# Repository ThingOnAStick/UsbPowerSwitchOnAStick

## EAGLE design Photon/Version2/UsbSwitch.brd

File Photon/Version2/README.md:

Usb Power Switch On A Stick
---------------------------

Control USB Power outlet to 2 USB A sockets via Photon.

Faults:
* V2.01
** ....
* V2.00
** 3v3 not connected to off board connector (D6/D6/GND/VBatt/RST/3v3).
** Excess top layer fill at Photon Keepout shown on PCB view (pdf issue only)

Changes:
* V2.00 - Added second USB A Socket. Removed current monitor, Added jumpers for TX/RX + 5V, A3-A5 + 5V, D6-D7 + 3v3 + RST and VBatt. New board size. Added gnd screen to USB A sockets.
* V2.01
** Fixed missing 3v3 trace for JP1. Improved silk screen. 
** Breaking: Moved control/flag D1-D4 -> D2-D5. Added JP4 to export D0/D1 for SDA/SCL or Switch 1+2 external. With 3v3 and 5V on connector.
** Moved JP1/2/3 to have 0.1" grid seperation between JP1 side and JP2/3. Moved JP4 to be on 0.1" grid with JP1/2/3 to allow for daughter board fitting on top with easy 0.1 grid.
** Beefed up vias for GND connection between USB Plug and PCB Bottom.
** Increased USB -> IC2 power trace to 0.05 (from 0.04)
** Moved Socket B -> R2 voltage monitor input via to be at top of board rather than crossing Photon Keepout area

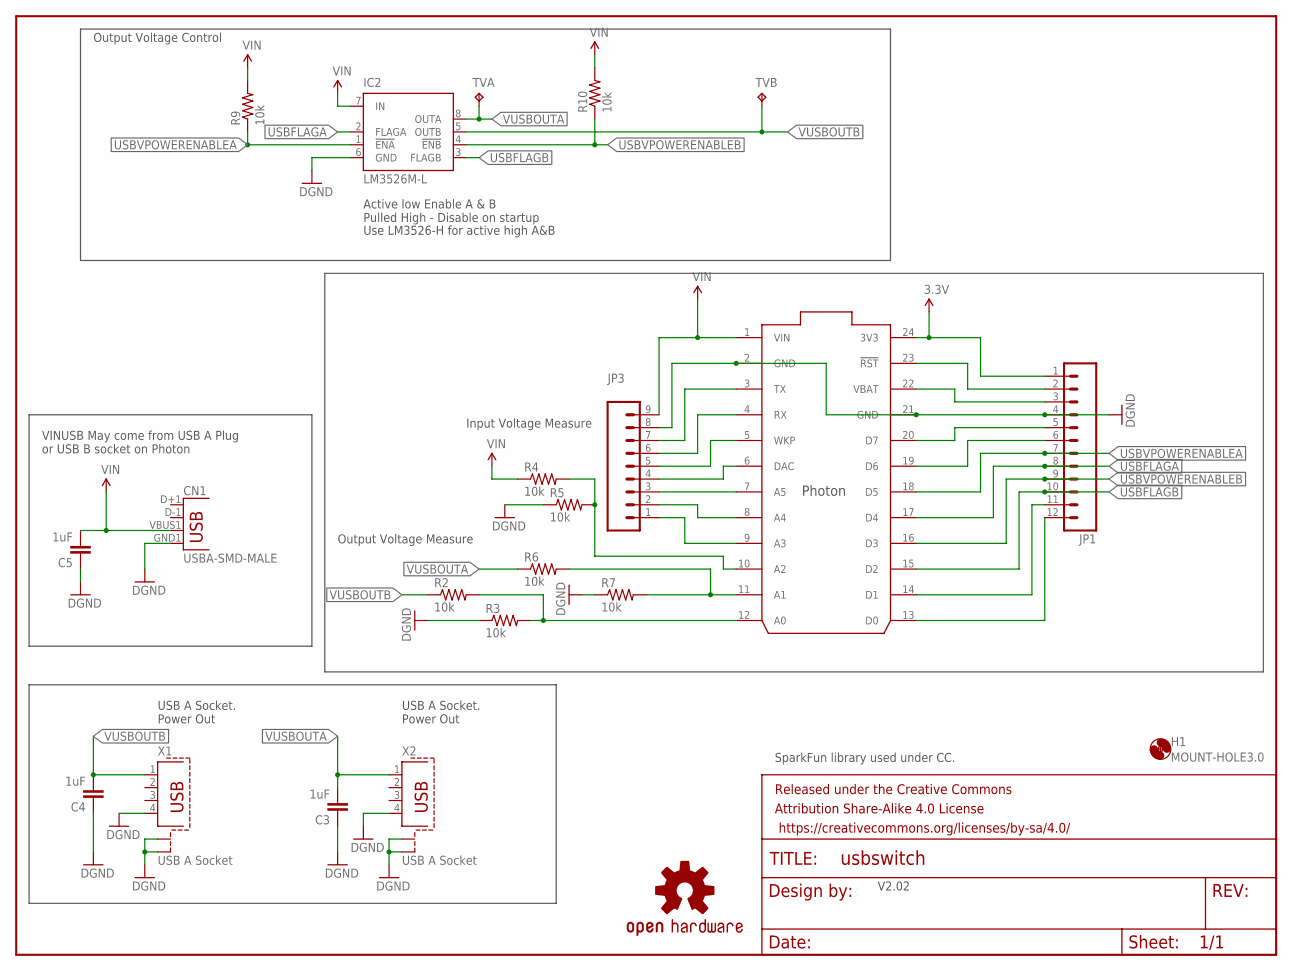
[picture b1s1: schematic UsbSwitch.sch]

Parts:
C3, C4, C5: 1uF; 0805
CN1: USBA-SMD-MALE; USB-A-SMT-MALE
FRAME2: FRAME-LETTER; CREATIVE_COMMONS
H1: MOUNT-HOLE3.0; 3,0
IC1: PHOTON
IC2: LM3526M-L; SO08
JP1: M12PTH; 1X12
JP3: M09; 1X09
LOGO2: OSHW-LOGOM; OSHW-LOGO-M
R2, R3, R4, R5, R6, R7, R9, R10: 10k; 1206
TVA: TPTP20SQ; TP20SQ
TVB: TPTP20SQ; TP20SQ
X1, X2: USB A Socket; PN87520-S

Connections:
3.3V: IC1.24 (3V3), JP1.1
GND: C3.1, C4.1, C5.1, CN1.GND1 (GND), IC1.2 (GND), IC1.21 (GND), IC2.6 (GND), JP1.4, JP3.8, R3.1, R5.1, R7.1, X1.4, X1.S1, X1.S2, X2.4, X2.S1, X2.S2
unnamed: IC1.6 (DAC), JP3.4
unnamed: IC1.5 (WKP), JP3.5
unnamed: IC1.4 (RX), JP3.6
unnamed: IC1.11 (A1), R6.2, R7.2
unnamed: IC1.9 (A3), JP3.1
unnamed: IC1.8 (A4), JP3.2
unnamed: IC1.7 (A5), JP3.3
unnamed: IC1.19 (D6), JP1.6
unnamed: IC1.20 (D7), JP1.5
unnamed: IC1.22 (VBAT), JP1.3
unnamed: IC1.23 (!RST), JP1.2
unnamed: IC1.3 (TX), JP3.7
unnamed: IC1.12 (A0), R2.2, R3.2
unnamed: IC1.10 (A2), R4.2, R5.2
SCL/SWITCH2: IC1.14 (D1), JP1.11
SDA/SWITCH1: IC1.13 (D0), JP1.12
USBFLAGA: IC1.17 (D4), IC2.2 (FLAGA), JP1.8
USBFLAGB: IC1.15 (D2), IC2.3 (FLAGB), JP1.10
USBVPOWERENABLEA: IC1.18 (D5), IC2.1 (!ENA), JP1.7, R9.1
USBVPOWERENABLEB: IC1.16 (D3), IC2.4 (!ENB), JP1.9, R10.1
VIN: C5.2, CN1.VBUS1 (VBUS), IC1.1 (VIN), IC2.7 (IN), JP3.9, R4.1, R9.2, R10.2
VUSBOUTA: C3.2, IC2.8 (OUTA), R6.1, TVA.TP, X2.1
VUSBOUTB: C4.2, IC2.5 (OUTB), R2.1, TVB.TP, X1.1

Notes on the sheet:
VINUSB May come from USB A Plug or USB B socket on Photon
USB A Socket. Power Out
Output Voltage Measure
Input Voltage Measure
Output Voltage Control
V2.02
Active low Enable A & B Pulled High - Disable on startup
Use LM3526-H for active high A&B
SparkFun library used under CC.

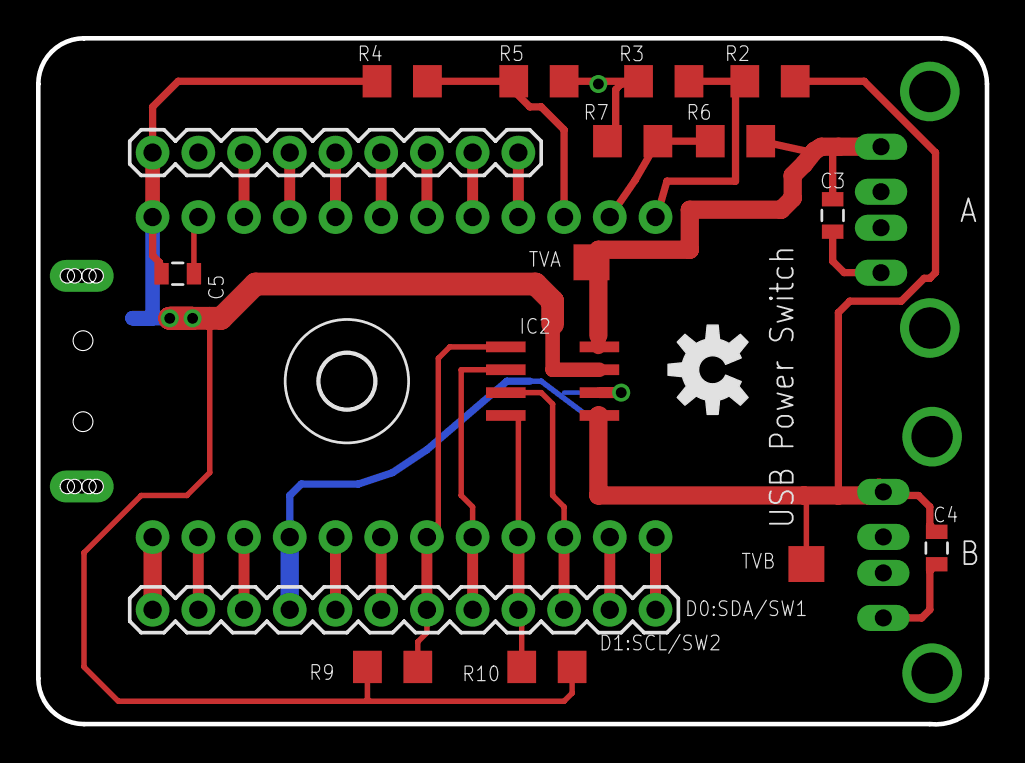
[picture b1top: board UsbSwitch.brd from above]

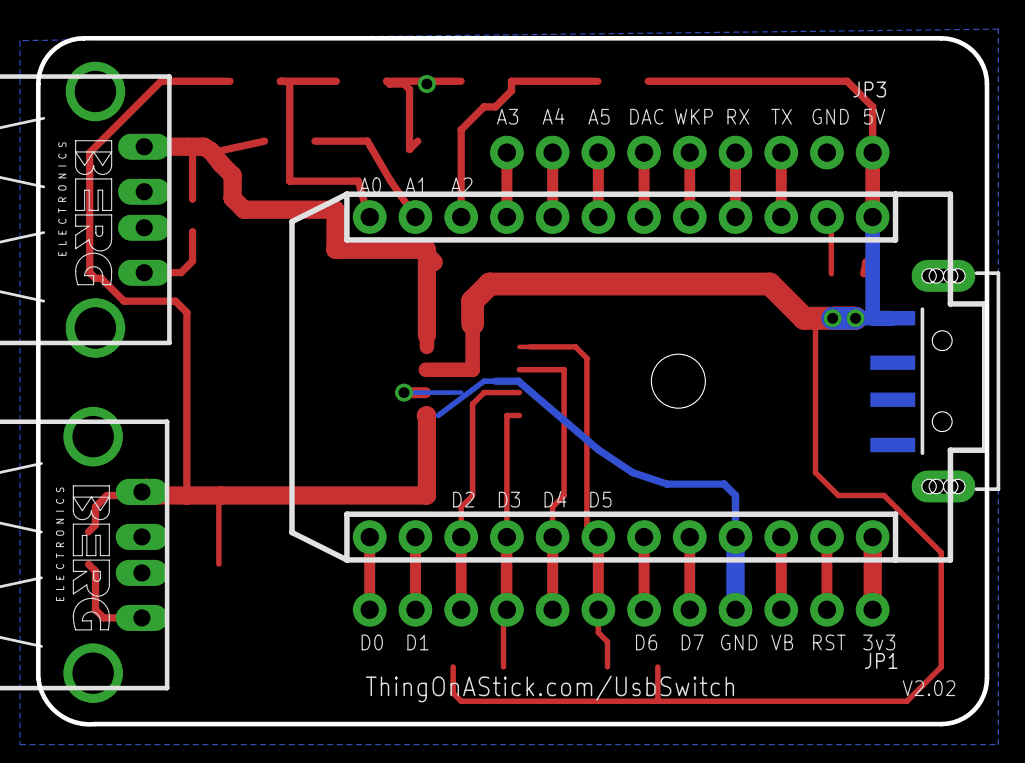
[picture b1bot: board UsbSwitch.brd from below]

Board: 2 copper layers, 52.7 x 38.1 mm, 23 parts (4 on the bottom side), 25 nets.

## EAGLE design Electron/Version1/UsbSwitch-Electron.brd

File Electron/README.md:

# UsbPowerSwitchOnAStick
Control USB Power via Photon/Electron on a USB Stick design.

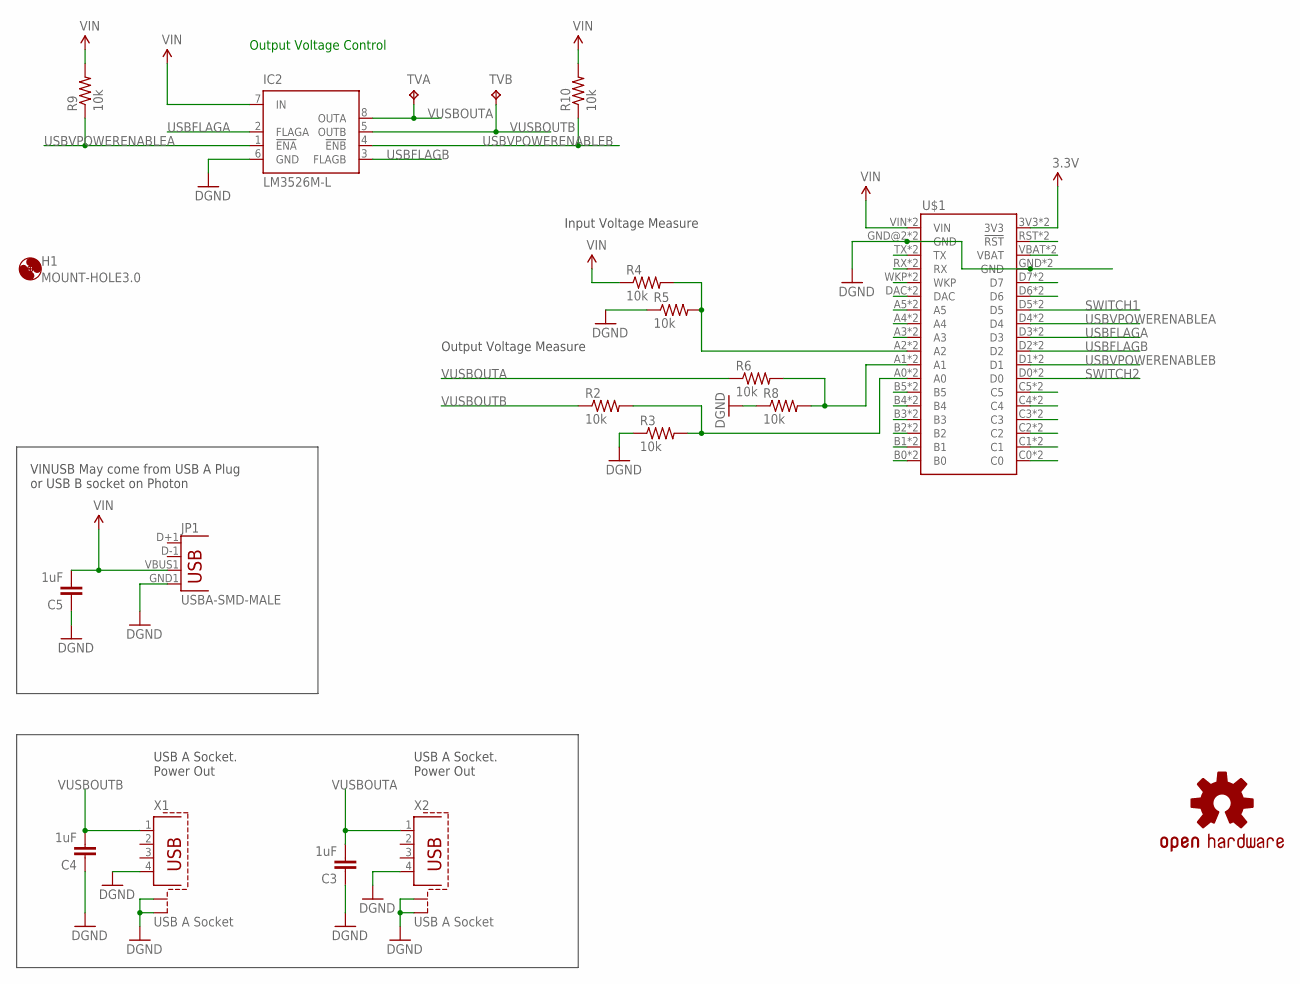
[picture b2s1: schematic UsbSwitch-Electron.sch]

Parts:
C3, C4, C5: 1uF; 0805
H1: MOUNT-HOLE3.0; 3,0
IC2: LM3526M-L; SO08
JP1: USBA-SMD-MALE; USB-A-SMT-MALE
LOGO2: OSHW-LOGOM; OSHW-LOGO-M
R2, R3, R4, R5, R6, R8, R9, R10: 10k; 1206
TVA: TPTP20SQ; TP20SQ
TVB: TPTP20SQ; TP20SQ
U$1: ELECTRONDUALNAMED; ELECTRON_SIMPLE_SILK_NAMES_DUAL
X1, X2: USB A Socket; PN87520-S

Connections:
3.3V: U$1.3V3, U$1.3V3_1 (3V3)
GND: C3.1, C4.1, C5.1, IC2.6 (GND), JP1.GND1 (GND), R3.1, R5.1, R8.1, U$1.GND, U$1.GND@2 (GND), U$1.GND_1 (GND), U$1.GND_1B (GND), X1.4, X1.S1, X1.S2, X2.4, X2.S1, X2.S2
unnamed: U$1.TX, U$1.TX_1 (TX)
unnamed: R6.2, R8.2, U$1.A1, U$1.A1_1 (A1)
unnamed: U$1.RX, U$1.RX_1 (RX)
unnamed: U$1.WKP, U$1.WKP_1 (WKP)
unnamed: U$1.DAC, U$1.DAC_1 (DAC)
unnamed: U$1.D6, U$1.D6_1 (D6)
unnamed: U$1.D7, U$1.D7_1 (D7)
unnamed: U$1.VBAT, U$1.VBATT_1 (VBAT)
unnamed: U$1.RST (!RST), U$1.RST_1 (!RST)
unnamed: U$1.C5, U$1.C5_1 (C5)
unnamed: U$1.C4, U$1.C4_1 (C4)
unnamed: U$1.C3, U$1.C3_1 (C3)
unnamed: R2.2, R3.2, U$1.A0, U$1.A0_1 (A0)
unnamed: U$1.C2, U$1.C2_1 (C2)
unnamed: R4.2, R5.2, U$1.A2, U$1.A2_1 (A2)
unnamed: U$1.C1, U$1.C1_1 (C1)
unnamed: U$1.C0, U$1.C0_1 (C0)
unnamed: U$1.A5, U$1.A5_1 (A5)
unnamed: U$1.A4, U$1.A4_1 (A4)
unnamed: U$1.A3, U$1.A3_1 (A3)
unnamed: U$1.B5, U$1.B5_1 (B5)
unnamed: U$1.B4, U$1.B4_1 (B4)
unnamed: U$1.B3, U$1.B3_1 (B3)
unnamed: U$1.B2, U$1.B2_1 (B2)
unnamed: U$1.B1, U$1.B1_1 (B1)
unnamed: U$1.B0, U$1.B0_1 (B0)
SWITCH1: U$1.D5, U$1.D5_1 (D5)
SWITCH2: U$1.D0, U$1.D0_1 (D0)
USBFLAGA: IC2.2 (FLAGA), U$1.D3, U$1.D3_1 (D3)
USBFLAGB: IC2.3 (FLAGB), U$1.D2, U$1.D2_1 (D2)
USBVPOWERENABLEA: IC2.1 (!ENA), R9.1, U$1.D4, U$1.D4_1 (D4)
USBVPOWERENABLEB: IC2.4 (!ENB), R10.1, U$1.D1, U$1.D1_1 (D1)
VIN: C5.2, IC2.7 (IN), JP1.VBUS1 (VBUS), R4.1, R9.2, R10.2, U$1.VIN, U$1.VIN_1B (VIN)
VUSBOUTA: C3.2, IC2.8 (OUTA), R6.1, TVA.TP, X2.1
VUSBOUTB: C4.2, IC2.5 (OUTB), R2.1, TVB.TP, X1.1

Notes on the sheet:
VINUSB May come from USB A Plug or USB B socket on Photon
USB A Socket. Power Out
Output Voltage Measure
Input Voltage Measure
Output Voltage Control

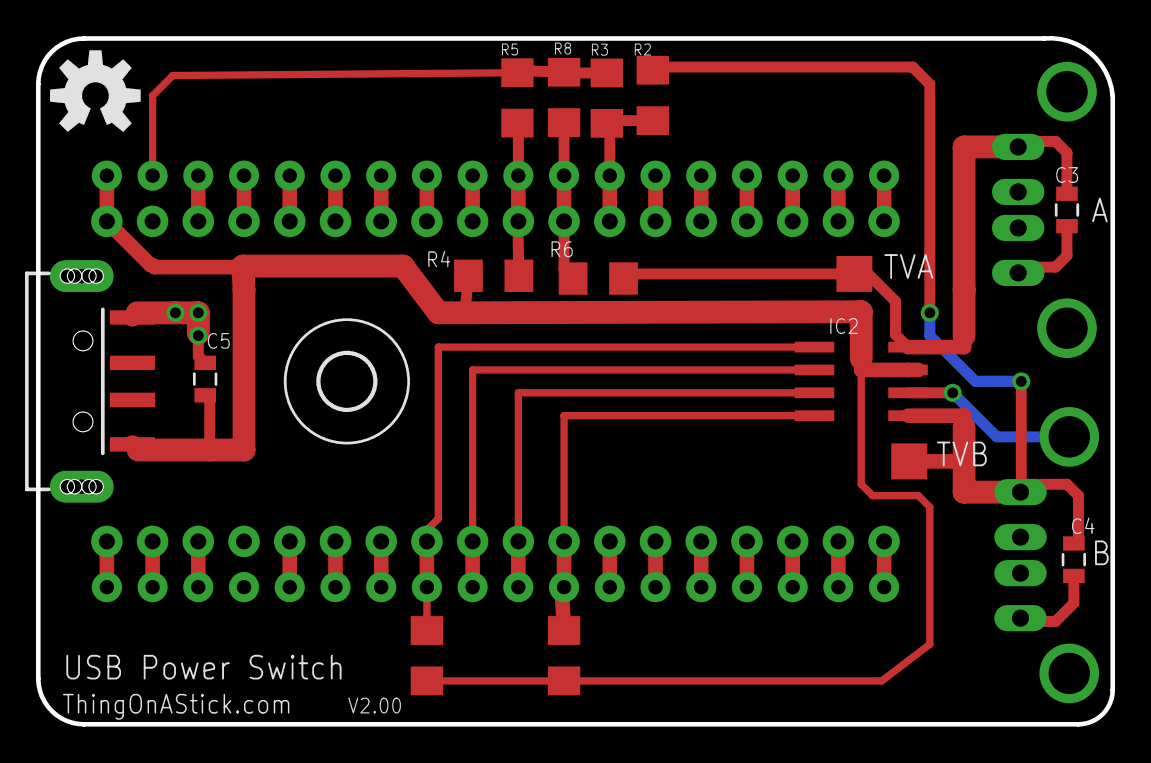
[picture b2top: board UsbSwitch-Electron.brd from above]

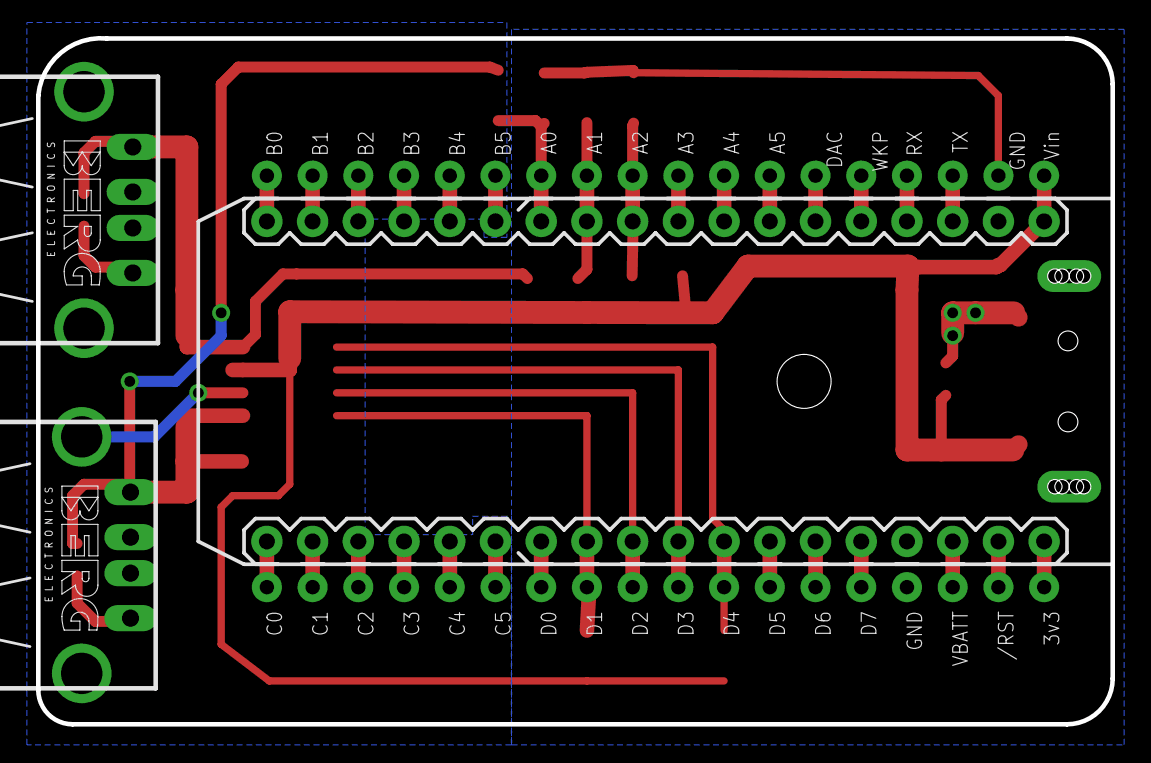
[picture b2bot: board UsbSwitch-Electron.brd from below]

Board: 2 copper layers, 59.7 x 38.1 mm, 20 parts (3 on the bottom side), 37 nets.

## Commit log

2015-12-06 Version 2.00 as sent to OSH Park.
2015-12-06 Added readme.
2015-12-14 Initial version of electron USB switch
2015-12-14 Updated readme for photon version
2016-01-28 Moved USB connector to top bottom side of PCB so that the Photon sticks out from the wall when put in a wall plug and that the USB in/out is not flipped.
    Moved USB controller chip inside the photon and put connectors for the photon pins all along appropriate pins.
2016-01-28 Added LM3526 datasheet.

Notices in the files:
parts and their libraries:
SparkFun-Connectors: Licensing: Creative Commons ShareAlike 4.0 International - https://creativecommons.org/licenses/by-sa/4.0
SparkFun-Aesthetics: Released under the Creative Commons Attribution Share-Alike 4.0 License
SparkFun-Aesthetics: https://creativecommons.org/licenses/by-sa/4.0
